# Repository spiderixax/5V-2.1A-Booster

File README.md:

# 5V-2.1A-Booster
A simple and tiny 5V step-up module capable of 2.1A output current based on the RT4812 chip.

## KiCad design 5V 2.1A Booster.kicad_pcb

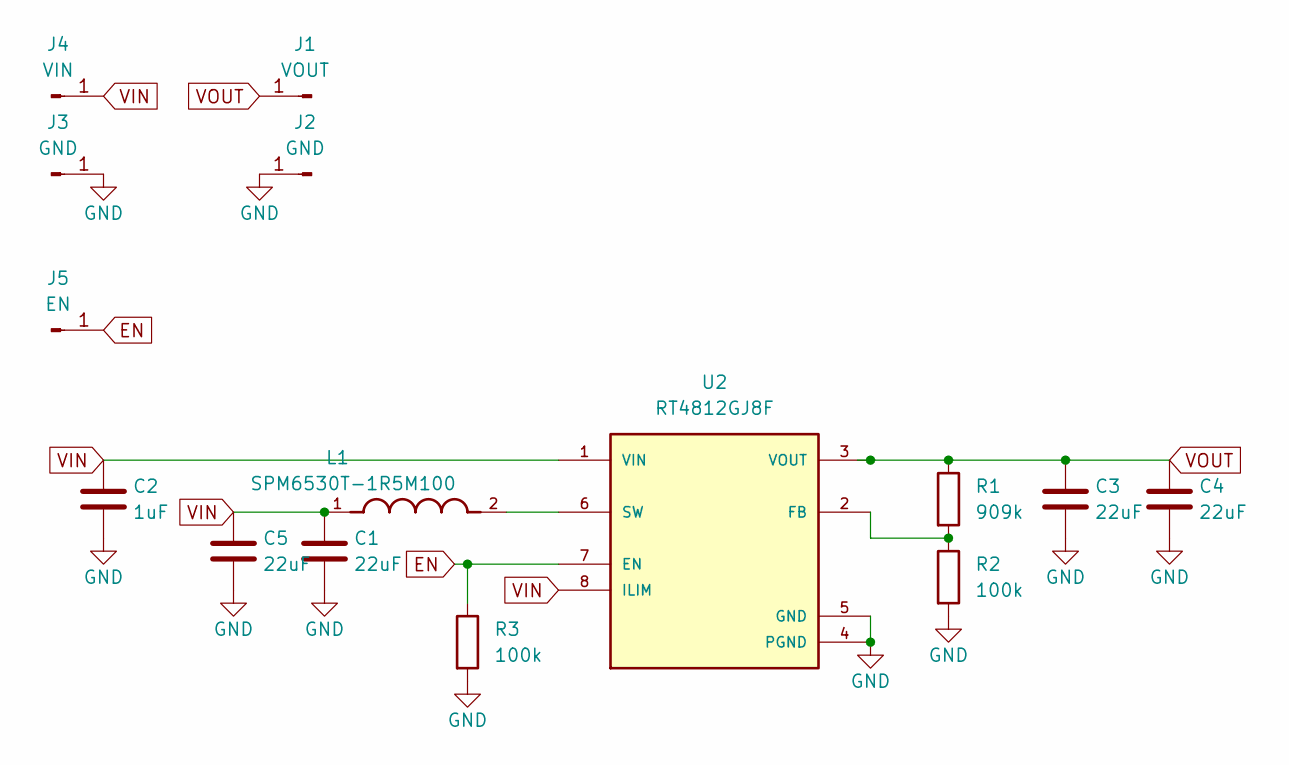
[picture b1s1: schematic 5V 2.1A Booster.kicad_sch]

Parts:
C1, C3, C4, C5: 22uF; C_0805_2012Metric; LCSC GRM21BR61C226ME44
C2: 1uF; C_0603_1608Metric
J1: VOUT; Solder_pad_4x3mm
J2, J3: GND; Solder_pad_4x3mm
J4: VIN; Solder_pad_4x3mm
J5: EN; Solder_pad_4x3mm
L1: SPM6530T-1R5M100; IND_SPM6530T-1R5M100; PARTREV N/A
R1: 909k; R_0603_1608Metric
R2, R3: 100k; R_0603_1608Metric
U2: RT4812GJ8F; SOT65P279X100-8N; PARTREV March 2019

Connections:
EN: J5.1, R3.1, U2.7 (EN)
GND: C1.2, C2.2, C3.2, C4.2, C5.2, J2.1, J3.1, R2.2, R3.2, U2.4 (PGND), U2.5 (GND)
unnamed: R1.2, R2.1, U2.2 (FB)
unnamed: L1.2, U2.6 (SW)
VIN: C1.1, C2.1, C5.1, J4.1, L1.1, U2.1 (VIN), U2.8 (ILIM)
VOUT: C3.1, C4.1, J1.1, R1.1, U2.3 (VOUT)

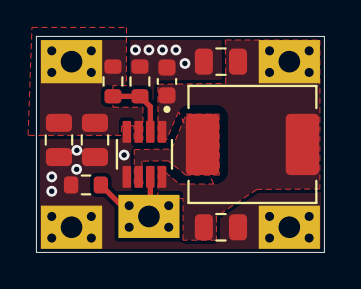
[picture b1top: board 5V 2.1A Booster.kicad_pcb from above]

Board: 2 copper layers, 16.0 x 12.0 mm, 15 parts (0 on the bottom side), 6 nets.

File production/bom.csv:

Designator,Footprint,Quantity,Value,LCSC Part #
"C1, C3, C4, C5",0805,4,22uF,GRM21BR61C226ME44
C2,0603,1,1uF,
J1,Solder_pad_4x3mm,1,VOUT,
"J2, J3",Solder_pad_4x3mm,2,GND,
J4,Solder_pad_4x3mm,1,VIN,
J5,Solder_pad_4x3mm,1,EN,
L1,IND_SPM6530T-1R5M100,1,SPM6530T-1R5M100,
R1,0603,1,909k,
"R2, R3",0603,2,100k,
U2,SOT65P279X100-8N,1,RT4812GJ8F,
